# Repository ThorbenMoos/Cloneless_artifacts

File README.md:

# Cloneless Artifacts
This repository contains PCB designs, FPGA controllers, verification collateral and software artifacts related to the Cloneless series of tamper-resistant open-source ASICs, in particular the [Cloneless1](https://github.com/ThorbenMoos/Cloneless1) chip.

## Layouts

## Photos

## Measurements

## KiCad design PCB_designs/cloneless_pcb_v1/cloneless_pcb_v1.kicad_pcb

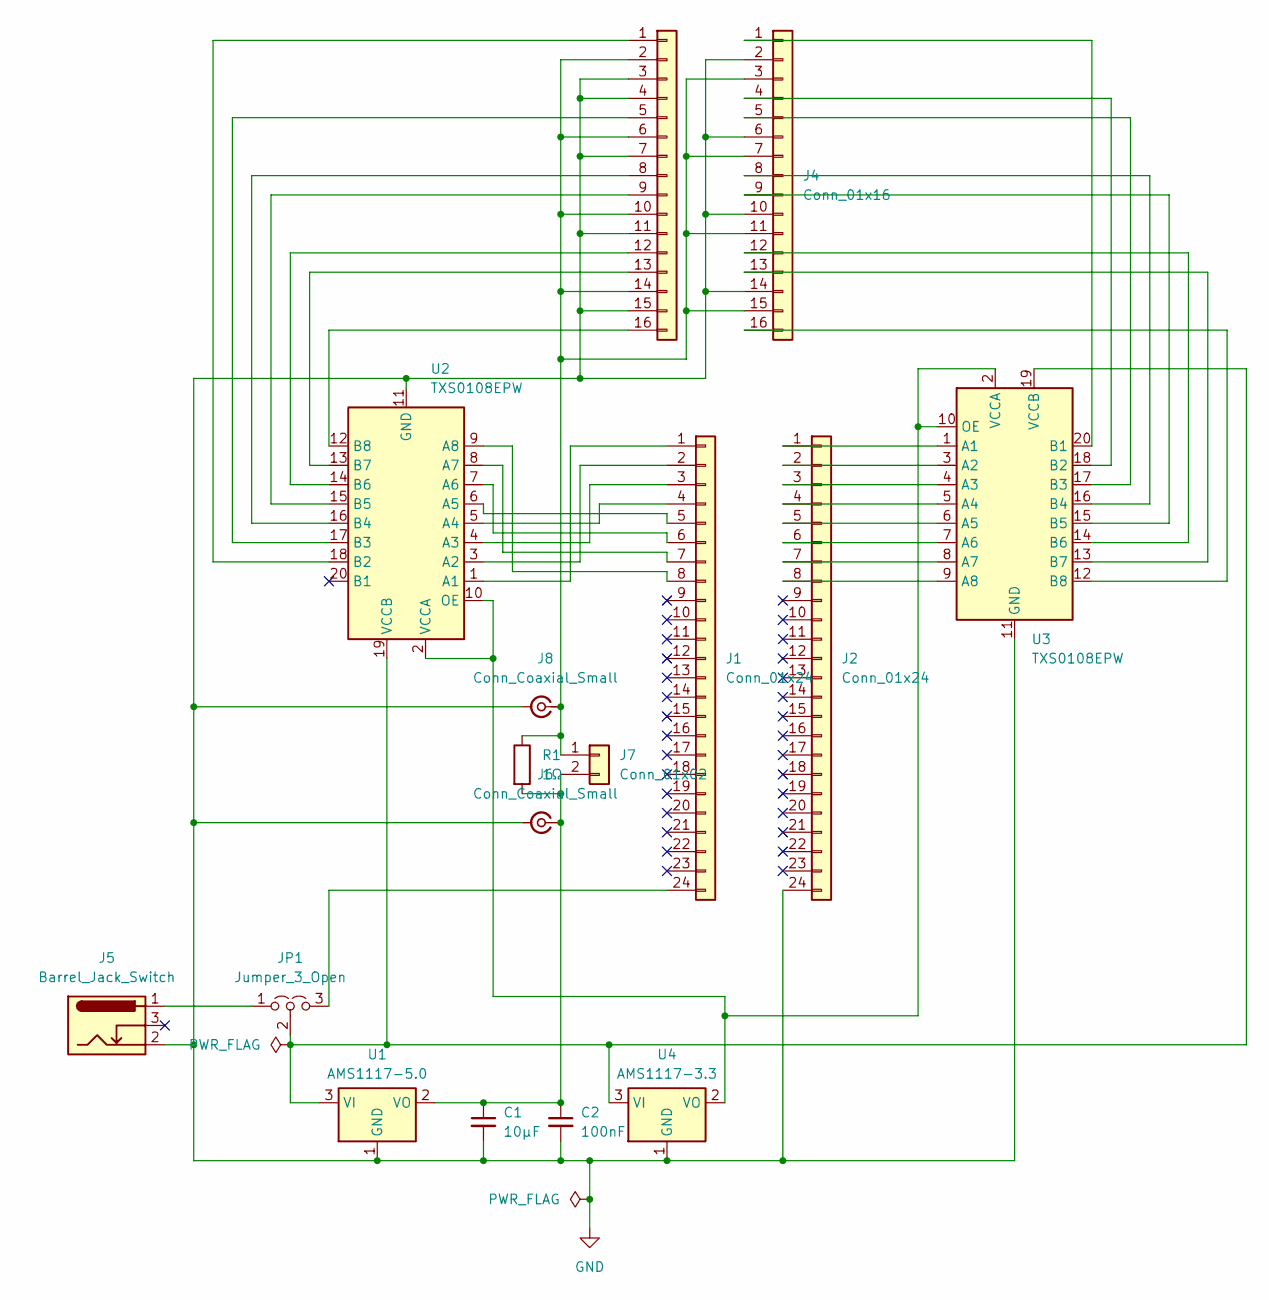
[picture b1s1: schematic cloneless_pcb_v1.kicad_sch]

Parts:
C1: 10µF; C_0805_2012Metric_Pad1.18x1.45mm_HandSolder
C2: 100nF; C_0805_2012Metric_Pad1.18x1.45mm_HandSolder
J1, J2: Conn_01x24; PinSocket_1x24_P2.54mm_Vertical
J3, J4: Conn_01x16; PinSocket_1x16_P2.54mm_Vertical
J5: Barrel_Jack_Switch; BarrelJack_Horizontal
J6, J8: Conn_Coaxial_Small; SMA_Wurth_60312002114503_Vertical
J7: Conn_01x02; PinHeader_1x02_P2.54mm_Vertical
JP1: Jumper_3_Open; PinHeader_1x03_P2.54mm_Vertical
R1: 1Ω; R_Axial_DIN0207_L6.3mm_D2.5mm_P10.16mm_Horizontal
U1: AMS1117-5.0; SOT-223-3_TabPin2
U2, U3: TXS0108EPW; TSSOP-20_4.4x6.5mm_P0.65mm
U4: AMS1117-3.3; SOT-223-3_TabPin2

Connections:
GND: C1.2, C2.2, J2.24, J3.3, J3.4, J3.7, J3.11, J3.15, J4.2, J4.6, J4.10, J4.14, J5.2, J6.2 (Ext), J8.2 (Ext), U1.1 (GND), U2.11 (GND), U3.11 (GND), U4.1 (GND)
unnamed: J1.1, U2.1 (A1)
unnamed: J1.2, U2.3 (A2)
unnamed: J1.3, U2.4 (A3)
unnamed: J1.4, U2.5 (A4)
unnamed: J1.5, U2.6 (A5)
unnamed: J1.6, U2.7 (A6)
unnamed: J1.7, U2.8 (A7)
unnamed: J1.8, U2.9 (A8)
unnamed: J1.24, JP1.3 (B)
unnamed: J2.1, U3.1 (A1)
unnamed: J2.2, U3.3 (A2)
unnamed: J2.3, U3.4 (A3)
unnamed: J2.4, U3.5 (A4)
unnamed: J2.5, U3.6 (A5)
unnamed: J2.6, U3.7 (A6)
unnamed: J2.7, U3.8 (A7)
unnamed: J2.8, U3.9 (A8)
unnamed: J3.1, U2.18 (B2)
unnamed: J3.5, U2.17 (B3)
unnamed: J3.8, U2.16 (B4)
unnamed: J3.9, U2.15 (B5)
unnamed: J3.2, J3.6, J3.10, J3.14, J4.3, J4.7, J4.11, J4.15, J7.1, J8.1 (In), R1.1
unnamed: J3.12, U2.14 (B6)
unnamed: J3.13, U2.13 (B7)
unnamed: J3.16, U2.12 (B8)
unnamed: J4.1, U3.20 (B1)
unnamed: J4.4, U3.18 (B2)
unnamed: J4.5, U3.17 (B3)
unnamed: J4.8, U3.16 (B4)
unnamed: J4.9, U3.15 (B5)
unnamed: J4.12, U3.14 (B6)
unnamed: J4.13, U3.13 (B7)
unnamed: J4.16, U3.12 (B8)
unnamed: C1.1, C2.1, J6.1 (In), J7.2, R1.2, U1.2 (VO)
unnamed: J5.1, JP1.1 (A)
unnamed: JP1.2 (C), U1.3 (VI), U2.19 (VCCB), U3.19 (VCCB), U4.3 (VI)
unnamed: U2.2 (VCCA), U2.10 (OE), U3.2 (VCCA), U3.10 (OE), U4.2 (VO)

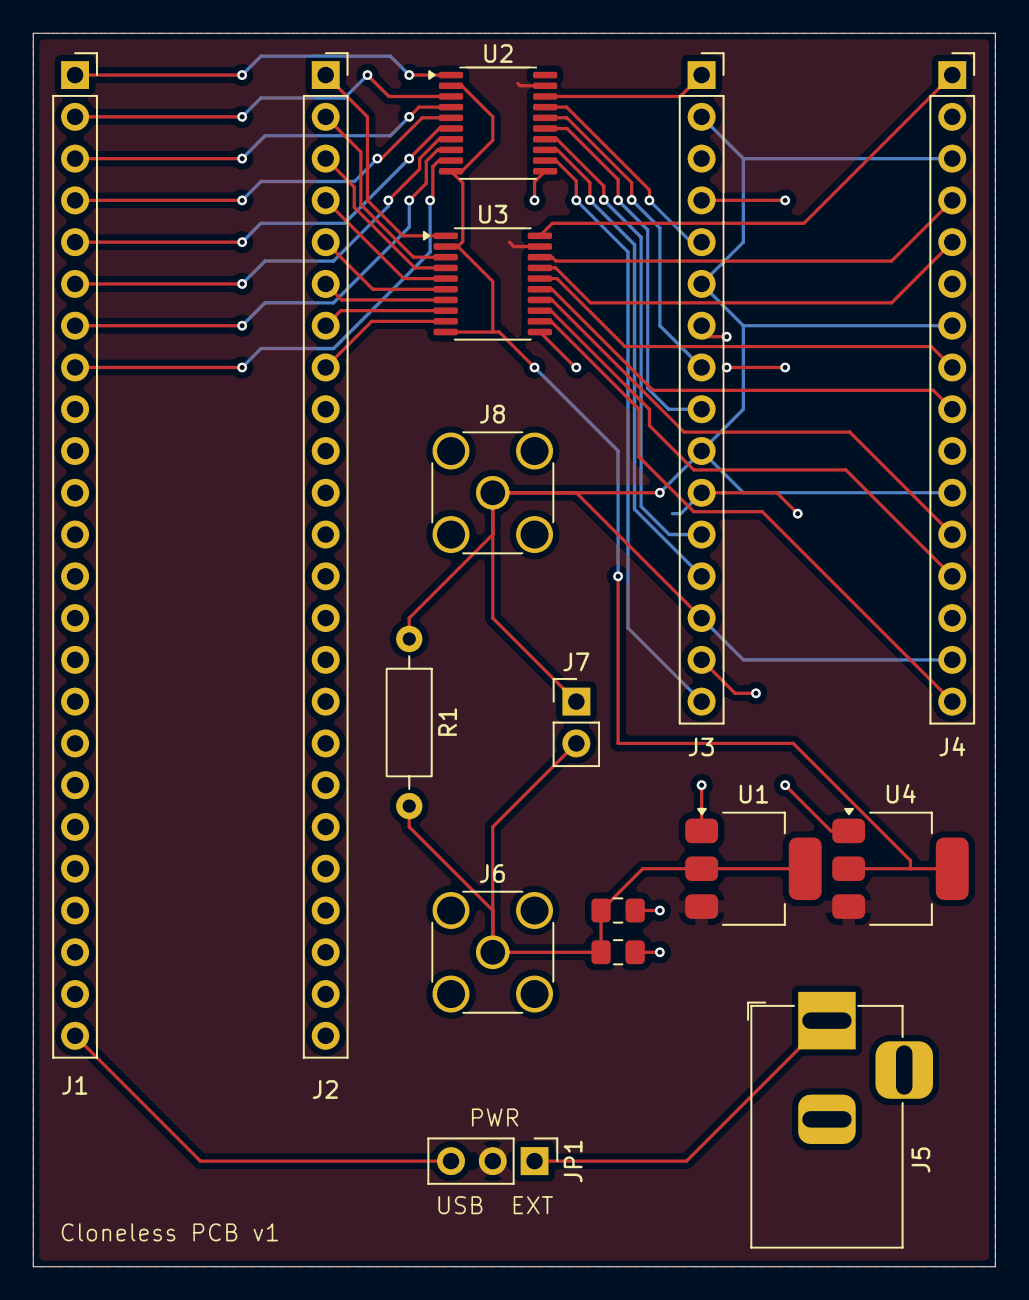
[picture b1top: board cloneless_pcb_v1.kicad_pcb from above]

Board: 2 copper layers, 58.5 x 75.0 mm, 16 parts (0 on the bottom side), 38 nets.

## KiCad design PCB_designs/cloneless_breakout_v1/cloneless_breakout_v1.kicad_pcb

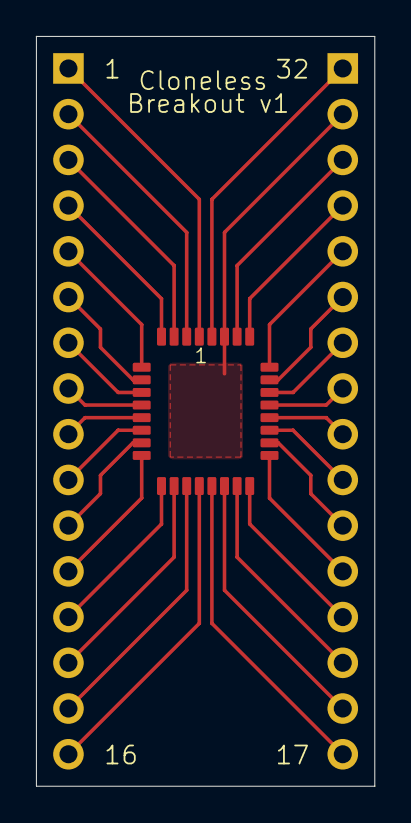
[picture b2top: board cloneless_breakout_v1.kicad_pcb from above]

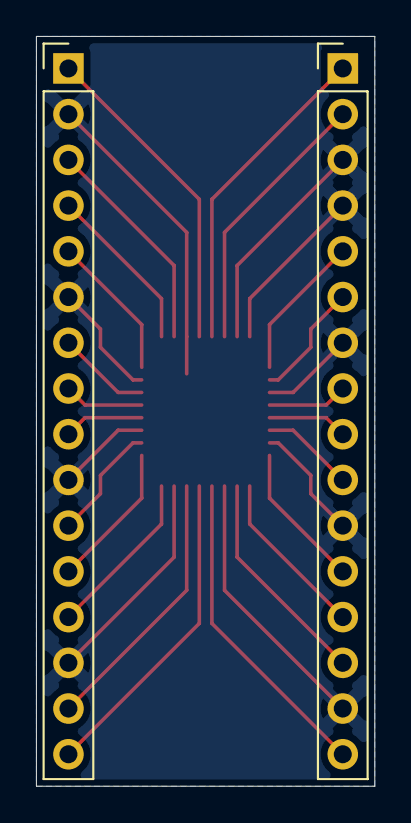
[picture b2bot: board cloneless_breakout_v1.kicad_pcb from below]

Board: 2 copper layers, 18.8 x 41.7 mm, 3 parts (2 on the bottom side), 24 nets.

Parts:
J1, J2: Conn_01x16; PinHeader_1x16_P2.54mm_Vertical
U1: cloneless

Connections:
GND: J1.3, J1.4, J1.7, J1.11, J1.15, J2.2, J2.6, J2.10, J2.14, U1.3 (VSS_1), U1.4 (VSS_9), U1.7 (VSS_2), U1.11 (VSS_3), U1.15 (VSS_4), U1.19 (VSS_5), U1.23 (VSS_6), U1.27 (VSS_7), U1.31 (VSS_8)
unnamed: J1.1, U1.1 (address_2)
unnamed: J1.2, U1.2 (VDD_1)
unnamed: J1.5, U1.5 (data_out_0)
unnamed: J1.6, U1.6 (VDD_2)
unnamed: J1.8, U1.8 (data_out_1)
unnamed: J1.9, U1.9 (data_out_2)
unnamed: J1.10, U1.10 (VDD_3)
unnamed: J1.12, U1.12 (data_out_3)
unnamed: J1.13, U1.13 (clk)
unnamed: J1.14, U1.14 (VDD_4)
unnamed: J1.16, U1.16 (rst)
unnamed: J2.1, U1.32 (address_1)
unnamed: J2.3, U1.30 (VDD_8)
unnamed: J2.4, U1.29 (address_0)
unnamed: J2.5, U1.28 (data_in_3)
unnamed: J2.7, U1.26 (VDD_7)
unnamed: J2.8, U1.25 (data_in_2)
unnamed: J2.9, U1.24 (data_in_1)
unnamed: J2.11, U1.22 (VDD_6)
unnamed: J2.12, U1.21 (data_in_0)
unnamed: J2.13, U1.20 (write)
unnamed: J2.15, U1.18 (VDD_5)
unnamed: J2.16, U1.17 (read)

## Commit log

2026-06-22 verification collateral added and folder names changed
2026-06-23 readme and pictures
2026-06-23 picture alignment in readme
2026-06-25 power trace added
2026-06-25 vector graphic power trace
2026-06-25 readme
